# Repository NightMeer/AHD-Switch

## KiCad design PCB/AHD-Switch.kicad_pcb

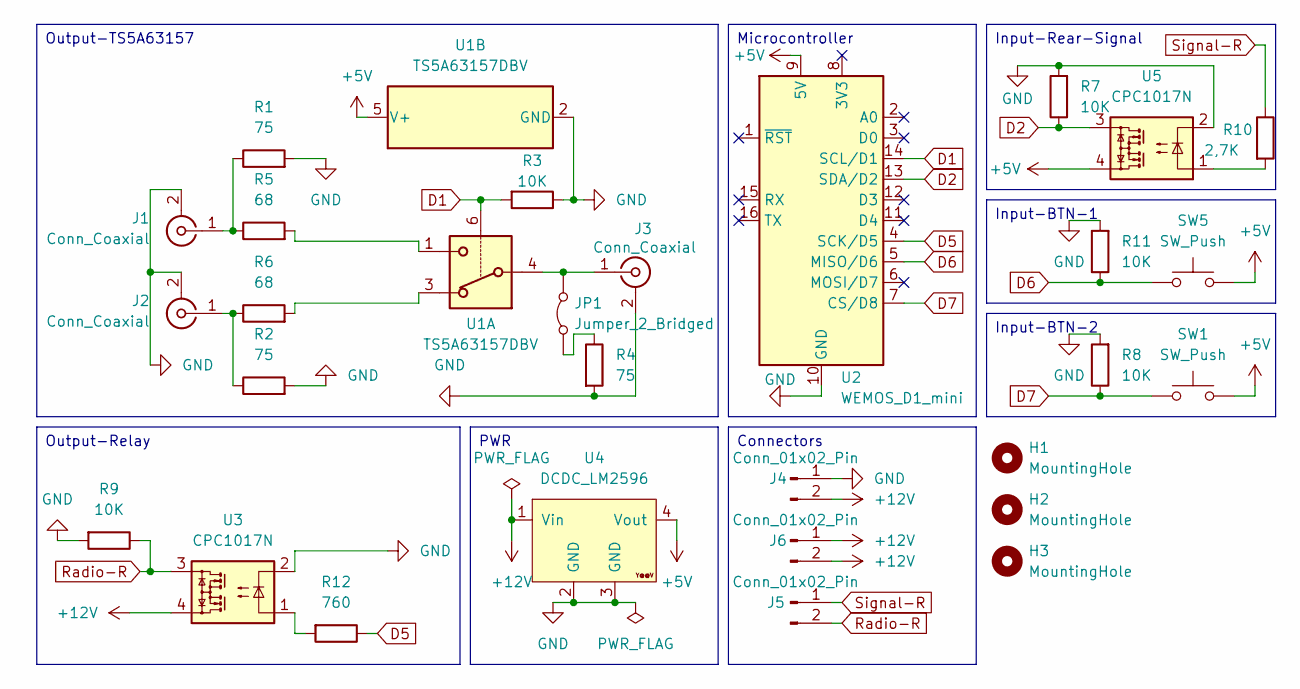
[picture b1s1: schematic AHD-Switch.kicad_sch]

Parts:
H1, H2, H3: MountingHole; MountingHole_3.2mm_M3
J1, J2, J3: Conn_Coaxial; CUI_RCJ-042
J4, J5, J6: Conn_01x02_Pin; HANDSON_KF301-2P
JP1: Jumper_2_Bridged; Jumper_2.54mm
R1, R2, R4: 75; R_Axial_DIN0207_L6.3mm_D2.5mm_P10.16mm_Horizontal
R3, R7, R8, R9, R11: 10K; R_Axial_DIN0207_L6.3mm_D2.5mm_P10.16mm_Horizontal
R5, R6: 68; R_Axial_DIN0207_L6.3mm_D2.5mm_P10.16mm_Horizontal
R10: 2,7K; R_Axial_DIN0207_L6.3mm_D2.5mm_P10.16mm_Horizontal
R12: 760; R_Axial_DIN0207_L6.3mm_D2.5mm_P10.16mm_Horizontal
SW1, SW5: SW_Push; HANDSON_KF301-2P
U1: TS5A63157DBV; SOT-23-6_Handsoldering
U2: WEMOS_D1_mini; WEMOS_D1_mini_light
U3, U5: CPC1017N; SOP-4_3.8x4.1mm_P2.54mm
U4: DCDC_LM2596

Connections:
+5V: SW1.2, SW5.2, U1.5 (V+), U2.9 (5V), U4.4 (Vout), U5.4
+12V: J4.2, J6.1, J6.2, U3.4, U4.1 (Vin)
D1: R3.2, U1.6, U2.14 (SCL/D1)
D2: R7.1, U2.13 (SDA/D2), U5.3
D5: R12.1, U2.4 (SCK/D5)
D6: R11.1, SW5.1, U2.5 (MISO/D6)
D7: R8.1, SW1.1, U2.7 (CS/D8)
GND: J1.2 (Ext), J2.2 (Ext), J3.2 (Ext), J4.1, R1.2, R2.2, R3.1, R4.2, R7.2, R8.2, R9.2, R11.2, U1.2 (GND), U2.10 (GND), U3.2, U4.2 (GND), U4.3 (GND), U5.2
unnamed: J1.1 (In), R1.1, R5.1
unnamed: J2.1 (In), R2.1, R6.1
unnamed: J3.1 (In), JP1.2 (B), U1.4
unnamed: JP1.1 (A), R4.1
unnamed: R5.2, U1.1
unnamed: R6.2, U1.3
unnamed: R10.2, U5.1
unnamed: R12.2, U3.1
Radio-R: J5.2, R9.1, U3.3
Signal-R: J5.1, R10.1

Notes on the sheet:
PWR
Connectors
Input-BTN-2
Output-TS5A63157
Microcontroller
Input-BTN-1
Output-Relay
Input-Rear-Signal

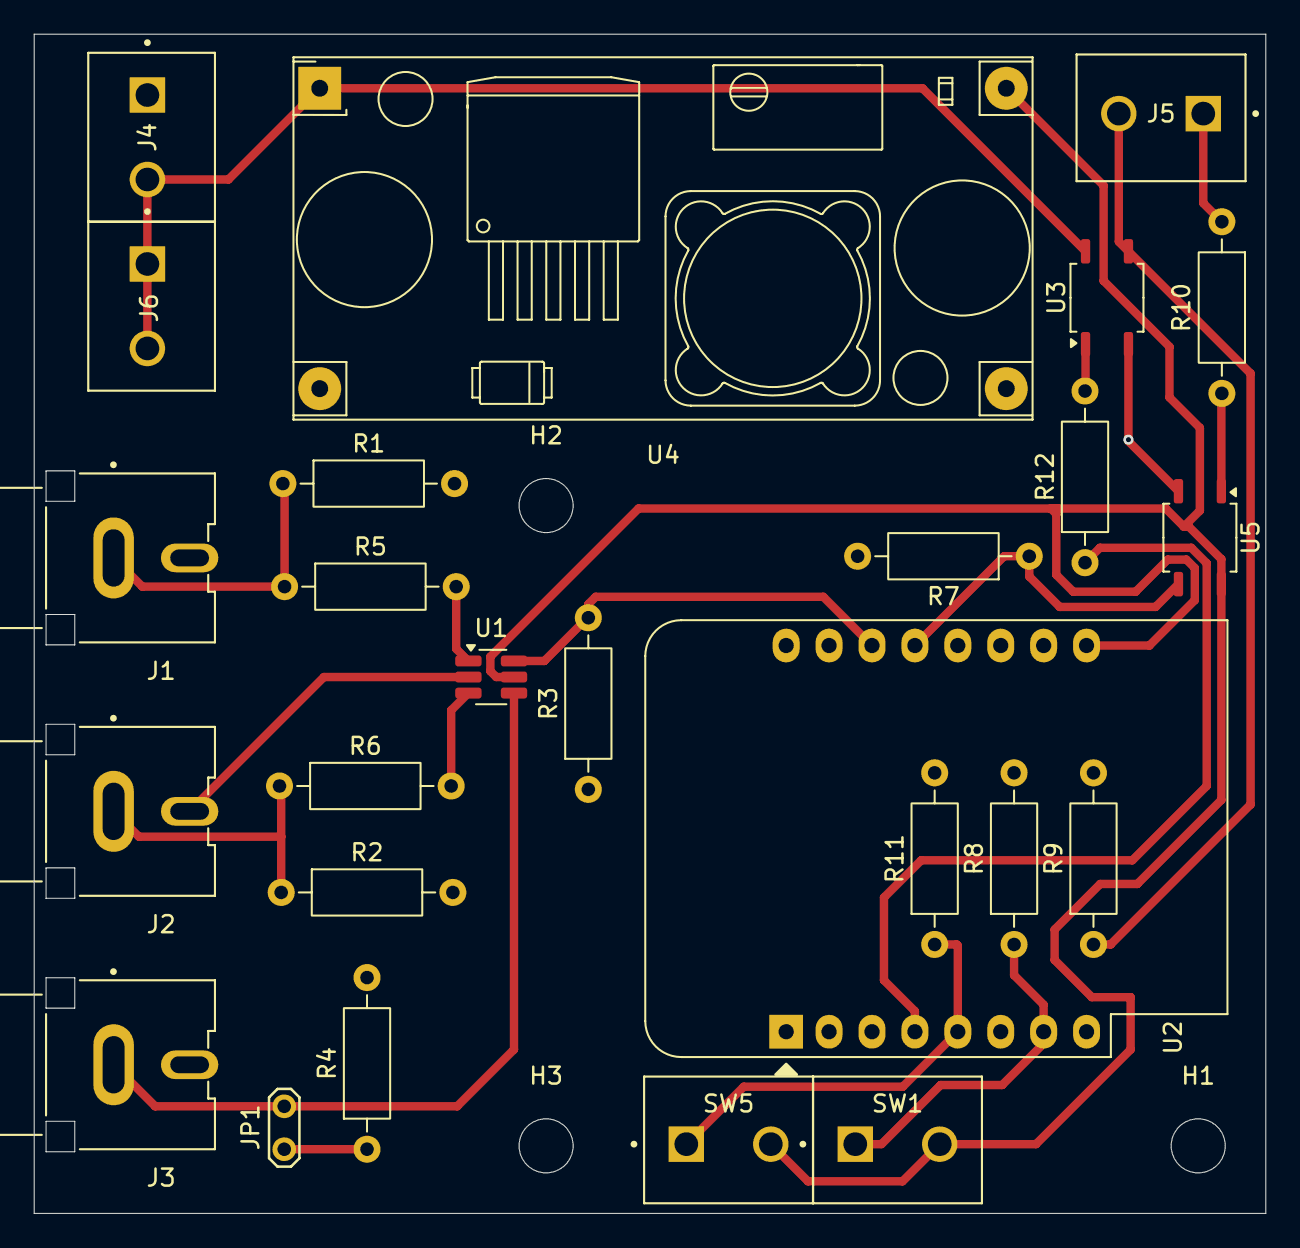
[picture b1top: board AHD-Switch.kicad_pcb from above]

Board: 2 copper layers, 72.9 x 69.8 mm, 29 parts (0 on the bottom side), 18 nets.

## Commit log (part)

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2025-07-07 Logik für AHD
2025-07-07 update files
2025-07-09 update§
2025-07-28 Final PCB
